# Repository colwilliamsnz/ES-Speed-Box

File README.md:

# ES-Speed-Box for controlling Pro-Ject Turntables with 16VAC Synchronous Motors.

## Status:

Prototype.

## Introduction:

A speed controller to suit Pro-Ject Turntables with 16VAC synchronous motors (Expression 3, etc). A clone of sorts of the off the shelf line of Pro-ject "SpeedBox" devices that allows for 33RPM and 45RPM speed selection electronically instead of changing the belt/pulley beneath the turntable platter.

Speed selection is controlled in software using a DDS (direct digital synthesis) IC to generate a sinusoidal waveform of the appropriate frequency (~50Hz for 33RPM, ~67 for 45RPM). An I2C header allows for an optional external OLED screen to display speed selection. An 18VDC output provides power to a Pro-Ject Phonobox. The device can be WiFi enabled to allow the speed to be controlled remotely using MQTT auto-discovery via HomeAssistant.

Power to the circuit is controlled via an SSR (solid state relay) and is intended to be connected to a 12V amplifier trigger output. Thus the device has no phantom power draw and only powers the turntable when the amplifier trigger output is on.

## Project Goals:

1. Powered on when the amplifier is on/phono aux input is on.
2. Provide power to both the turntable but also an Phono Box II pre-amp.
3. I2C interface to allow connection of an OLED screen to display speed and amp volume (amp volume via Yamaha API).
4. Low profile design to fit in a small rack mountable case.

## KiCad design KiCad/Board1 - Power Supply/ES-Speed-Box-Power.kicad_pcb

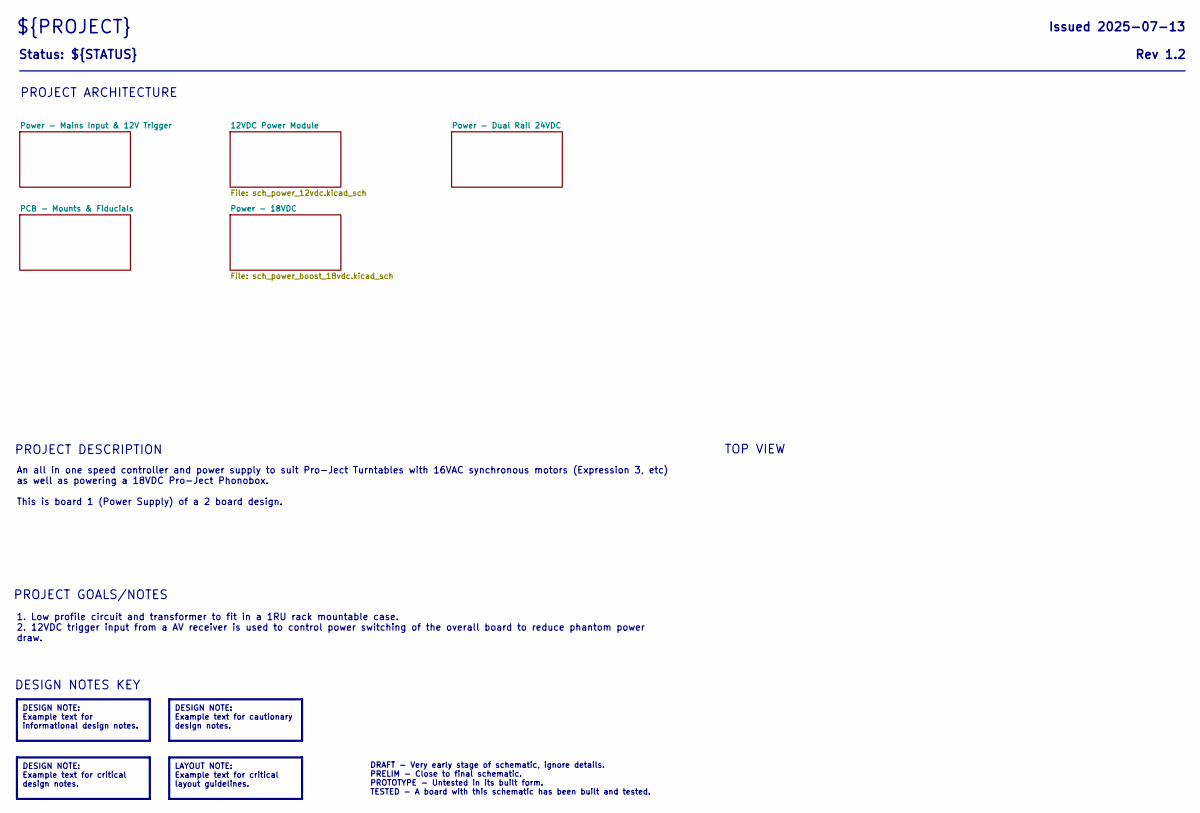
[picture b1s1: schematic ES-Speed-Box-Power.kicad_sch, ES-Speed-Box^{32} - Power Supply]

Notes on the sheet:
TOP VIEW
PROJECT DESCRIPTION
PROJECT GOALS/NOTES
PROJECT ARCHITECTURE
DESIGN NOTES KEY
${PROJECT}
Status: ${STATUS}
1. Low profile circuit and transformer to fit in a 1RU rack mountable case. 2. 12VDC trigger input from a AV receiver is used to control power switching of the overall board to reduce phantom power draw.
DESIGN NOTE: Example text for critical design notes.
DESIGN NOTE: Example text for cautionary design notes.
Issued ${ISSUE_DATE}
Rev ${REVISION}
LAYOUT NOTE: Example text for critical layout guidelines.
DRAFT - Very early stage of schematic, ignore details. PRELIM - Close to final schematic. PROTOTYPE - Untested in its built form. TESTED - A board with this schematic has been built and tested.
An all in one speed controller and power supply to suit Pro-Ject Turntables with 16VAC synchronous motors (Expression 3, etc) as well as powering a 18VDC Pro-Ject Phonobox. This is board 1 (Power Supply) of a 2 board design.
DESIGN NOTE: Example text for informational design notes.

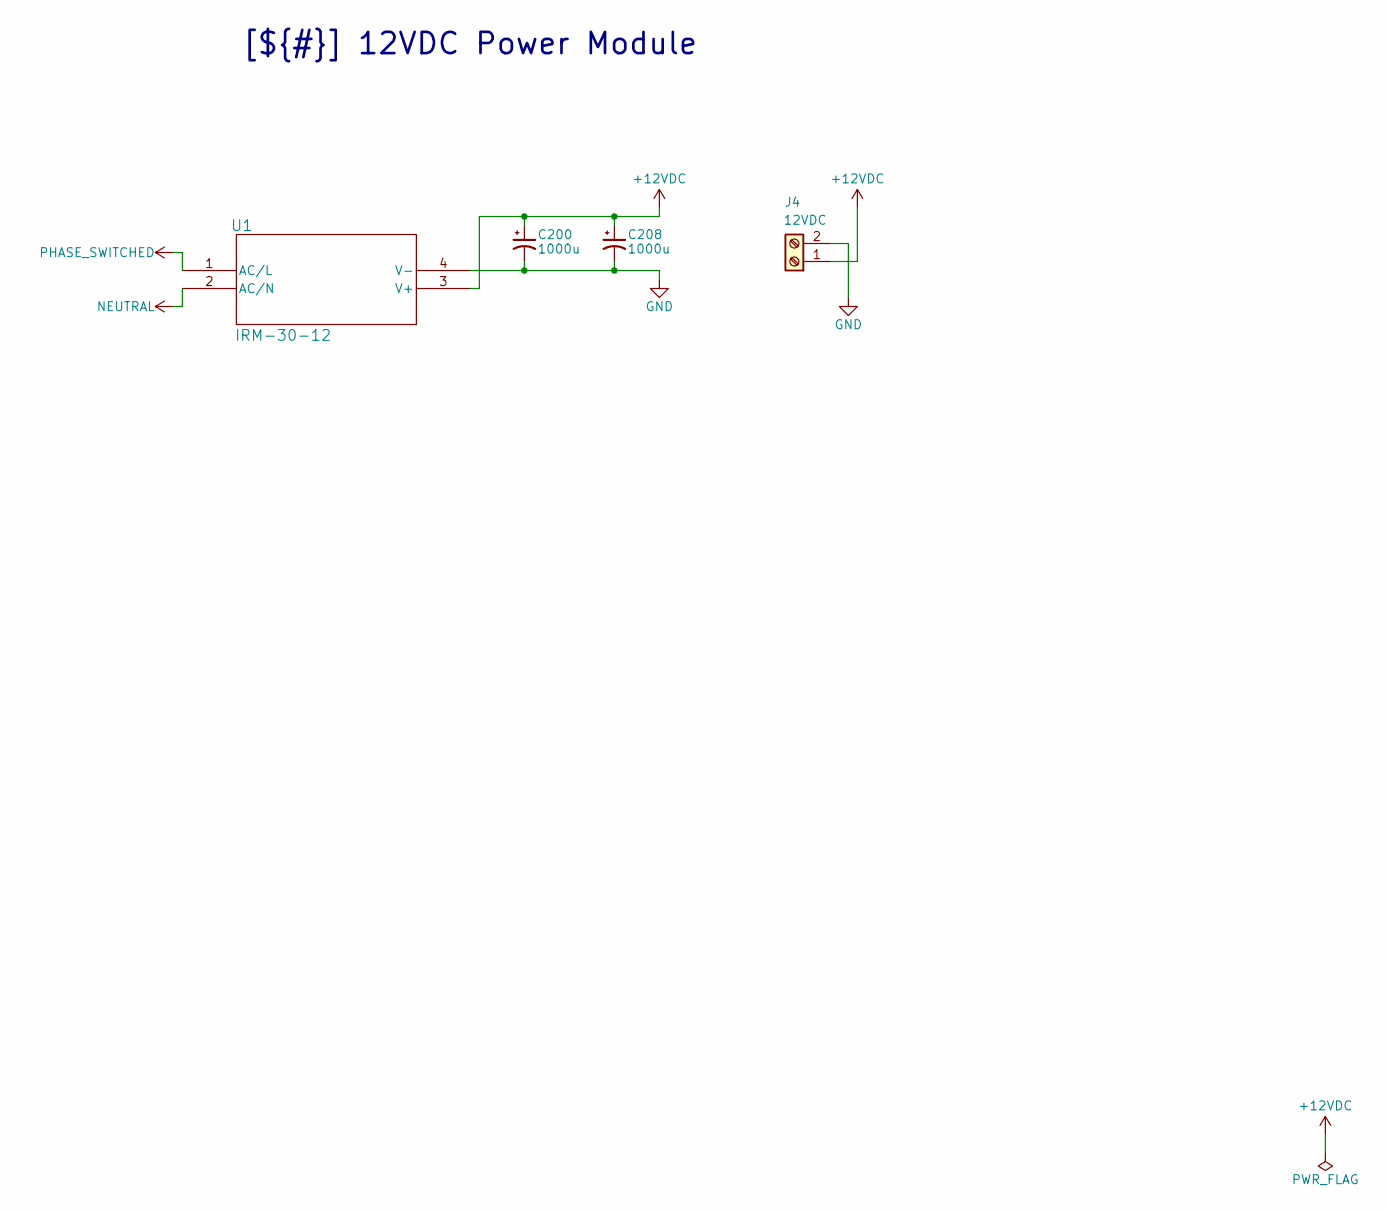
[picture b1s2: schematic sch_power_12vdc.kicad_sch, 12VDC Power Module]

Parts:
C200, C208: 1000u; CP_Radial_D13.0mm_P5.00mm
J4: 12VDC; TerminalBlock_1x02_P5.00mm
U1: IRM-30-12; Digikey_PN 1866-3043-ND

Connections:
+12VDC: C200.1, C208.1, J4.1, U1.3 (V+); also elsewhere on the board
GND: C200.2, C208.2, J4.2, U1.4 (V-); also elsewhere on the board
NEUTRAL: U1.2 (AC/N); also elsewhere on the board
PHASE_SWITCHED: U1.1 (AC/L); also elsewhere on the board

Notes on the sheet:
[${#}] ${TITLE}

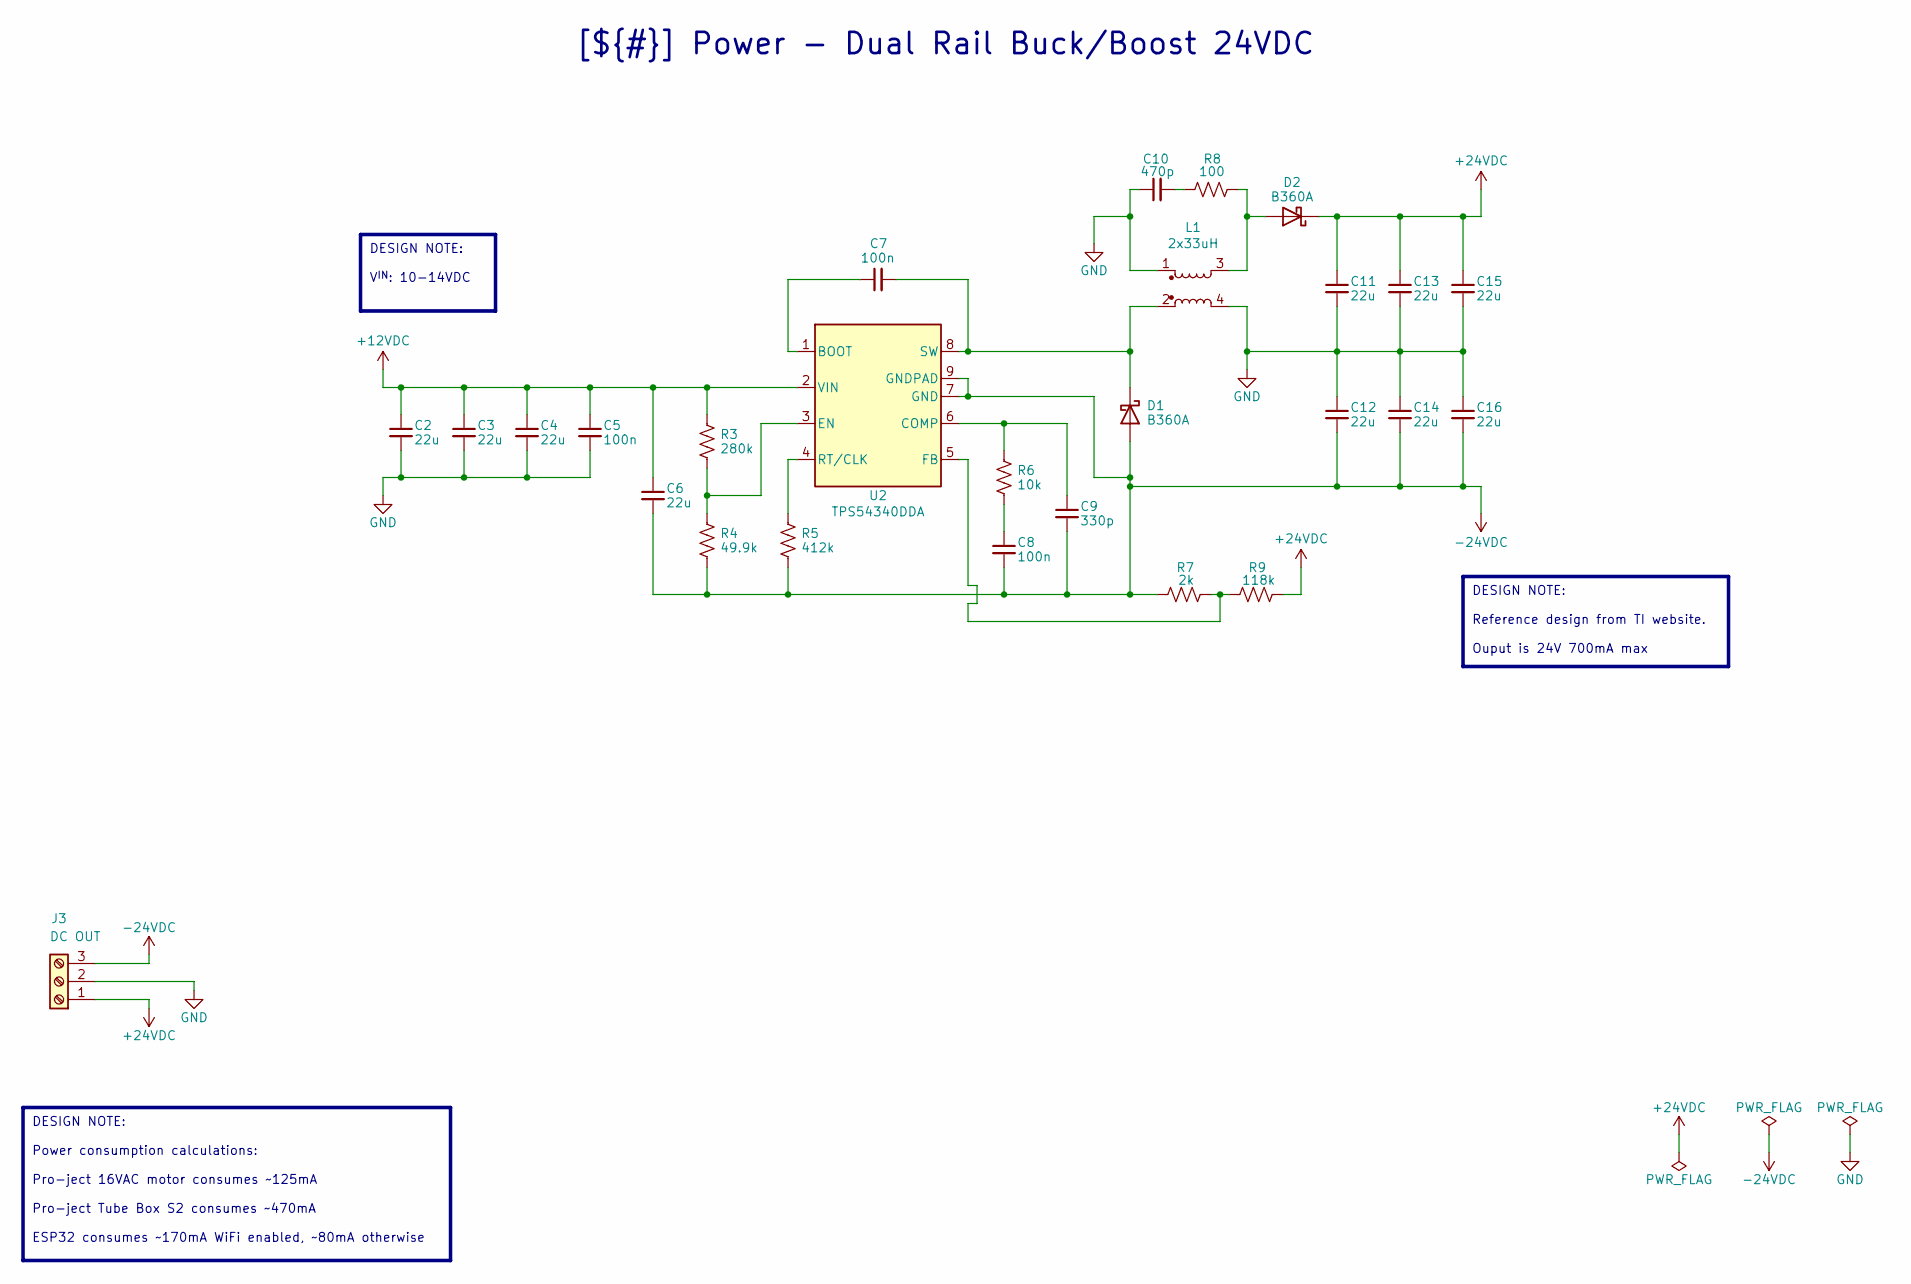
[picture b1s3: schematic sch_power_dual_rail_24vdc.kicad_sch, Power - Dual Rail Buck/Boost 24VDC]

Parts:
C2, C3, C4, C6, C11, C12, C13, C14, C15, C16: 22u; C_0805_2012Metric; Digikey_PN 445-14428-1-ND
C5, C7, C8: 100n; C_0603_1608Metric; Digikey_PN 587-3354-1-ND
C9: 330p; C_0603_1608Metric; Digikey_PN 399-C0603C331K5RACTUCT-ND
C10: 470p; C_0603_1608Metric; Digikey_PN 399-C0603C471F5GACTUCT-ND
D1, D2: B360A; D_SMA; Digikey_PN B360A-M3/61TGICT-ND
J3: DC OUT; TerminalBlock_1x03_P5.00mm
L1: 2x33uH; Bournes_SRF1260-330M; Digikey_PN SRF1260-330MCT-ND
R3: 280k; R_0603_1608Metric; Digikey_PN 311-280KHRCT-ND
R4: 49.9k; R_0603_1608Metric; Digikey_PN 541-3989-1-ND
R5: 412k; R_0603_1608Metric; Digikey_PN 311-412KHRCT-ND
R6: 10k; R_0603_1608Metric; Digikey_PN A121523CT-ND
R7: 2k; R_0603_1608Metric; Digikey_PN 541-3953-1-ND
R8: 100; R_0603_1608Metric; Digikey_PN 311-100HRCT-ND
R9: 118k; R_0603_1608Metric; Digikey_PN 541-118KHCT-ND
U2: TPS54340DDA; TI_SO-PowerPAD-8_ThermalVias; Digikey_PN 296-35495-5-ND

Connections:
+12VDC: C2.1, C3.1, C4.1, C5.1, C6.1, R3.1, U2.2 (VIN); also elsewhere on the board
+24VDC: C11.1, C13.1, C15.1, D2.1 (K), J3.1, R9.2
-24VDC: C6.2, C8.2, C9.2, C12.2, C14.2, C16.2, D1.2 (A), J3.3, R4.2, R5.2, R7.1, U2.7 (GND), U2.9 (GNDPAD)
GND: C2.2, C3.2, C4.2, C5.2, C10.1, C11.2, C12.1, C13.2, C14.1, C15.2, C16.1, J3.2, L1.1, L1.4; also elsewhere on the board
unnamed: C8.1, R6.2
unnamed: C10.2, R8.1
unnamed: C7.2, D1.1 (K), L1.2, U2.8 (SW)
unnamed: D2.2 (A), L1.3, R8.2
unnamed: C7.1, U2.1 (BOOT)
unnamed: C9.1, R6.1, U2.6 (COMP)
unnamed: R3.2, R4.1, U2.3 (EN)
unnamed: R7.2, R9.1, U2.5 (FB)
unnamed: R5.1, U2.4 (RT/CLK)

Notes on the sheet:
[${#}] ${TITLE}
DESIGN NOTE: Power consumption calculations: Pro-ject 16VAC motor consumes ~125mA Pro-ject Tube Box S2 consumes ~470mA ESP32 consumes ~170mA WiFi enabled, ~80mA otherwise
DESIGN NOTE: Reference design from TI website. Ouput is 24V 700mA max
DESIGN NOTE: V^{IN}: 10-14VDC

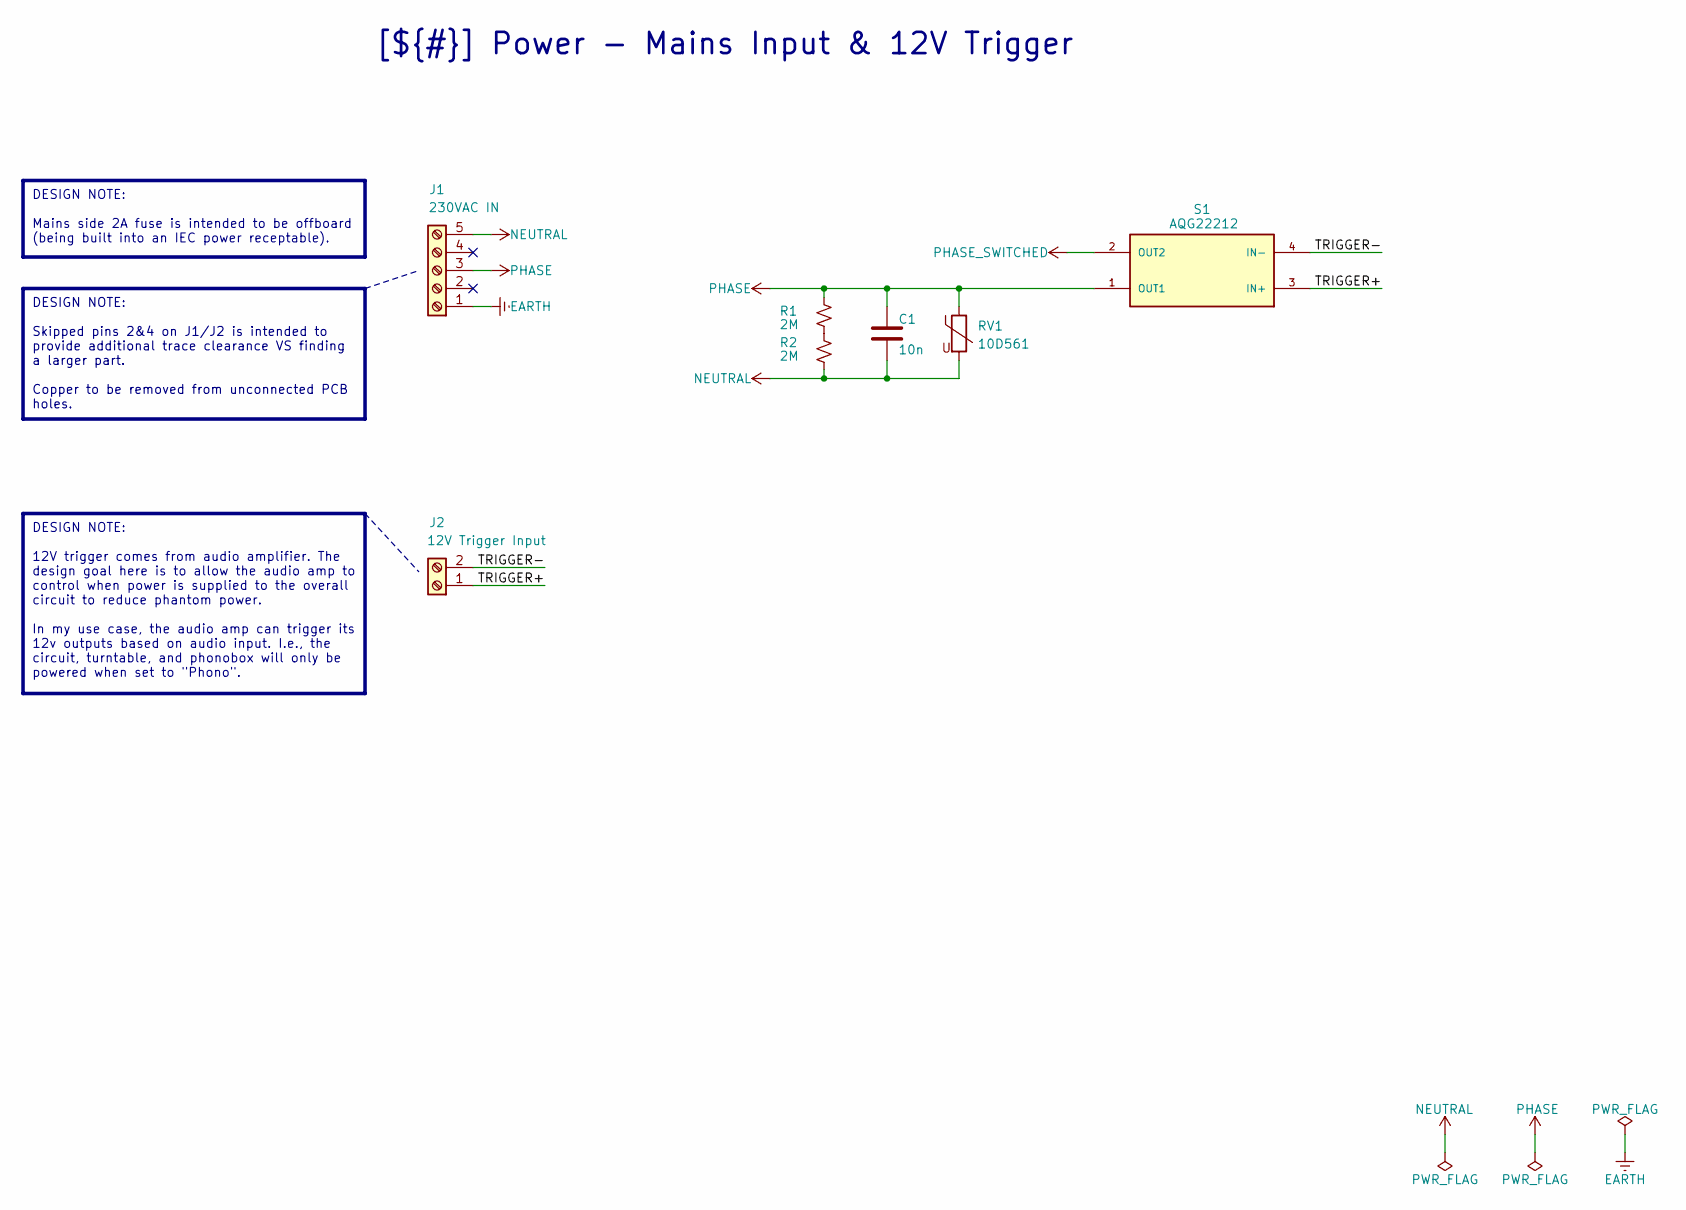
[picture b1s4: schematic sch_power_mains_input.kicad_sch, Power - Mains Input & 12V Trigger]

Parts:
C1: 10n; C_Rect_L18.0mm_W5.0mm_P15.00mm_FKS3_FKP3; Digikey_PN BFC233841103-ND
J1: 230VAC IN; TerminalBlock_1x05_P5.00mm
J2: 12V Trigger Input; TerminalBlock_1x02_P5.00mm
R1, R2: 2M; R_2010_5025Metric_Pad1.40x2.65mm_HandSolder; Digikey_PN 2019-HV732HTTE2004FCT-ND
RV1: 10D561; RV_Disc_D12mm_W6.1mm_P7.5mm; Digikey_PN 118-MOV-10D561K-ND
S1: AQG22212; Digikey_PN 255-3751-ND

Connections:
/Power - Mains Input & 12V Trigger/TRIGGER+: J2.1, S1.3 (IN+)
/Power - Mains Input & 12V Trigger/TRIGGER-: J2.2, S1.4 (IN-)
EARTH: J1.1
NEUTRAL: C1.2, J1.5, R2.2, RV1.2; also elsewhere on the board
unnamed: R1.2, R2.1
PHASE: C1.1, J1.3, R1.1, RV1.1, S1.1 (OUT1)
PHASE_SWITCHED: S1.2 (OUT2); also elsewhere on the board

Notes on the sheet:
DESIGN NOTE: Skipped pins 2&4 on J1/J2 is intended to provide additional trace clearance VS finding a larger part. Copper to be removed from unconnected PCB holes.
[${#}] ${TITLE}
DESIGN NOTE: 12V trigger comes from audio amplifier. The design goal here is to allow the audio amp to control when power is supplied to the overall circuit to reduce phantom power. In my use case, the audio amp can trigger its 12v outputs based on audio input. I.e., the circuit, turntable, and pho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
DESIGN NOTE: Mains side 2A fuse is intended to be offboard (being built into an IEC power receptable).

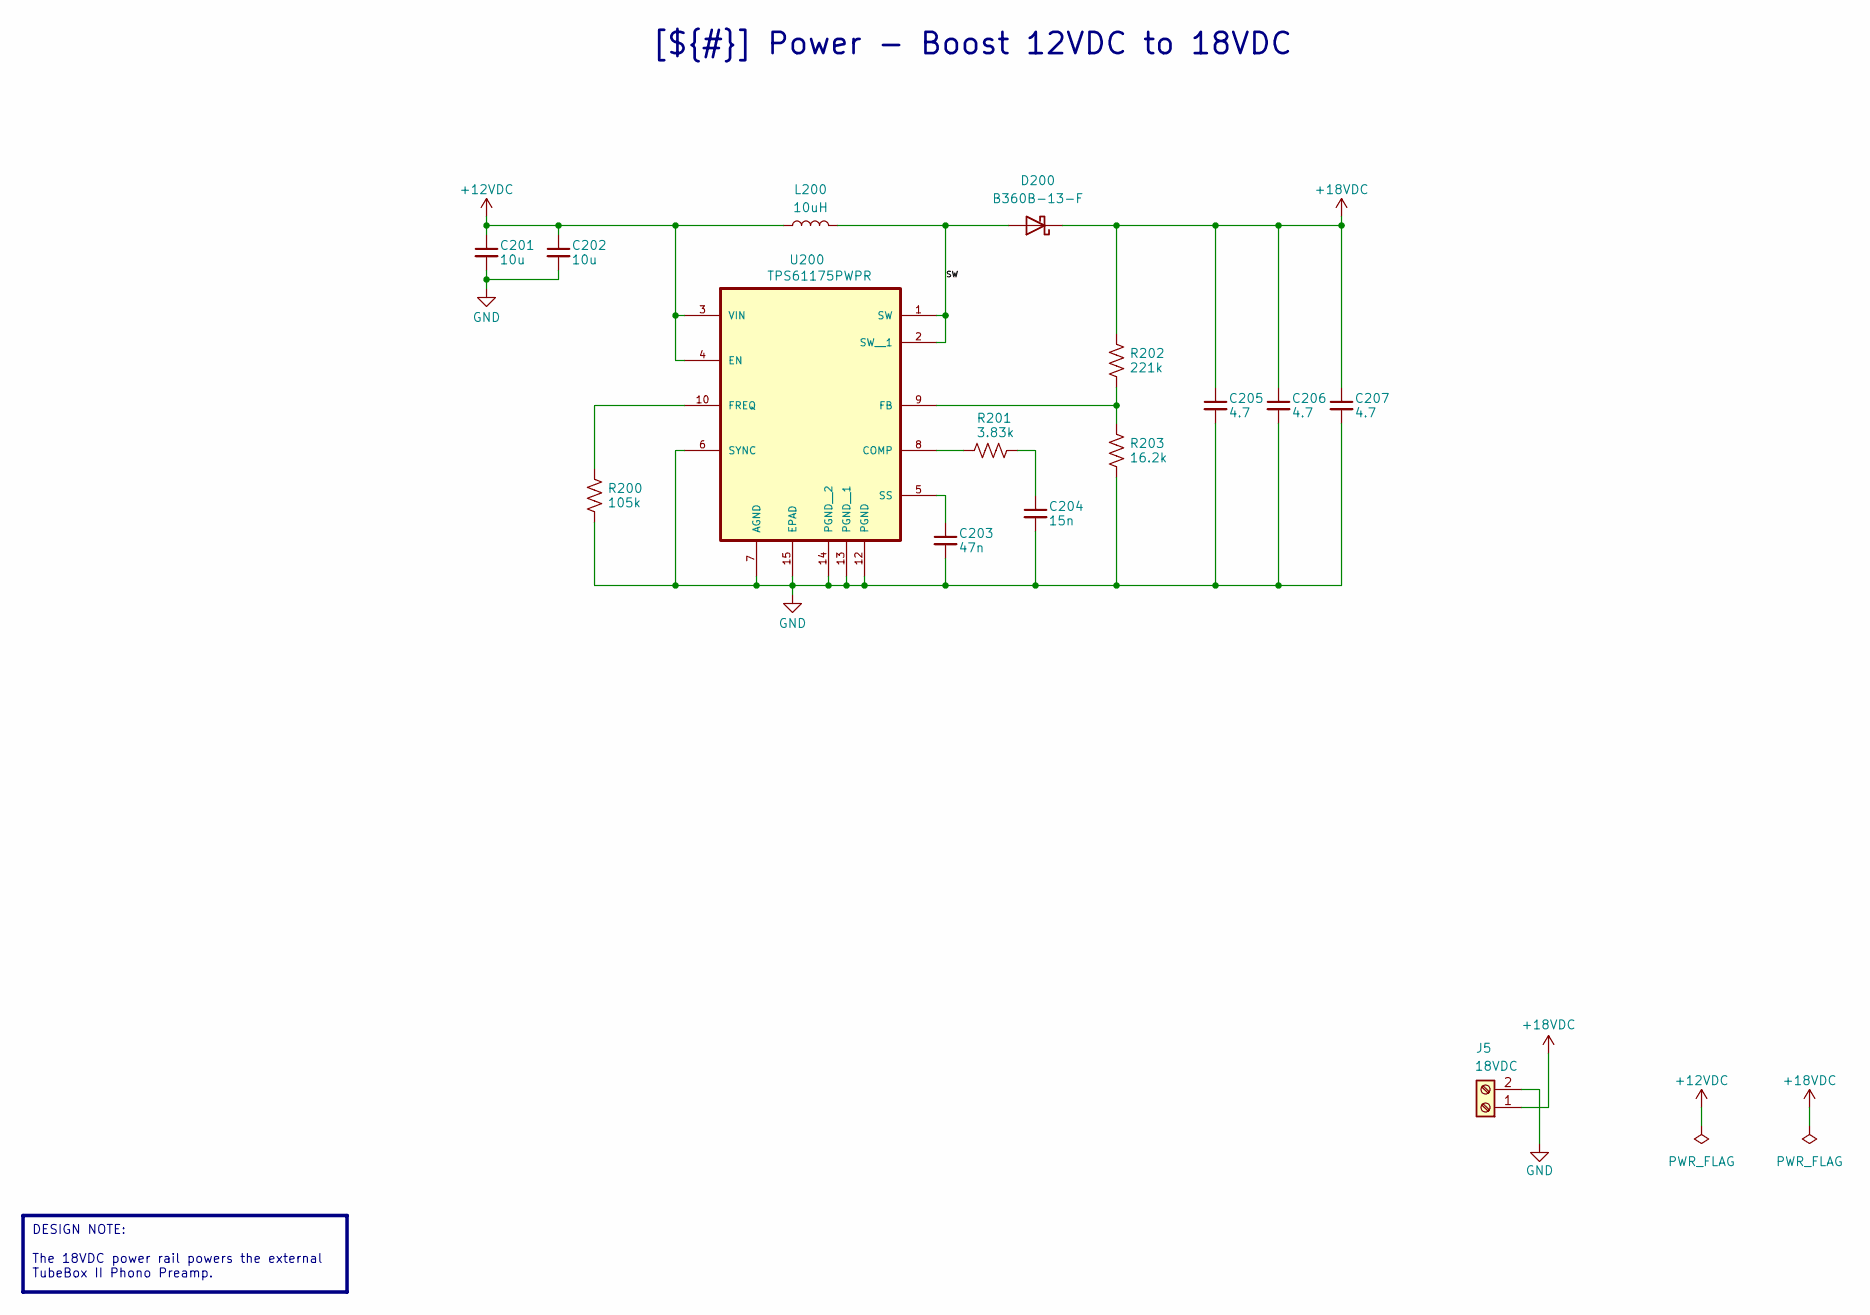
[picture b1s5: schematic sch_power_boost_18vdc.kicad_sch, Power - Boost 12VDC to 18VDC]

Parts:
C201, C202: 10u; C_0805_2012Metric; Digikey_PN 490-10515-1-ND
C203: 47n; C_0603_1608Metric; Digikey_PN 490-5854-1-ND
C204: 15n; C_0603_1608Metric; Digikey_PN 311-1430-1-ND
C205, C206, C207: 4.7; C_0805_2012Metric; Digikey_PN 490-10751-1-ND
D200: B360B-13-F; D_SMB; Digikey_PN B360B-FDICT-ND
J5: 18VDC; TerminalBlock_1x02_P5.00mm
L200: 10uH; Bournes_SRP5030T-100M; Digikey_PN SRP5030T-100MCT-ND
R200: 105k; R_0603_1608Metric; Digikey_PN 13-AC0603FR-07105KLCT-ND
R201: 3.83k; R_0603_1608Metric; Digikey_PN 311-3.83KHRCT-ND
R202: 221k; R_0603_1608Metric; Digikey_PN 311-221KHRCT-ND
R203: 16.2k; R_0603_1608Metric; Digikey_PN 311-16.2KHRCT-ND
U200: TPS61175PWPR; TPS61175; Digikey_PN 296-24013-1-ND

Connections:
+12VDC: C201.1, C202.1, L200.1, U200.3 (VIN), U200.4 (EN); also elsewhere on the board
+18VDC: C205.1, C206.1, C207.1, D200.1 (K), J5.1, R202.1
/Power - 18VDC/SW: D200.2 (A), L200.2, U200.1 (SW), U200.2 (SW__1)
GND: C201.2, C202.2, C203.2, C204.2, C205.2, C206.2, C207.2, J5.2, R200.2, R203.2, U200.6 (SYNC), U200.7 (AGND), U200.12 (PGND), U200.13 (PGND__1), U200.14 (PGND__2), U200.15 (EPAD); also elsewhere on the board
unnamed: C204.1, R201.2
unnamed: R201.1, U200.8 (COMP)
unnamed: R202.2, R203.1, U200.9 (FB)
unnamed: R200.1, U200.10 (FREQ)
unnamed: C203.1, U200.5 (SS)

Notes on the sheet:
DESIGN NOTE: The 18VDC power rail powers the external TubeBox II Phono Preamp.
[${#}] ${TITLE}

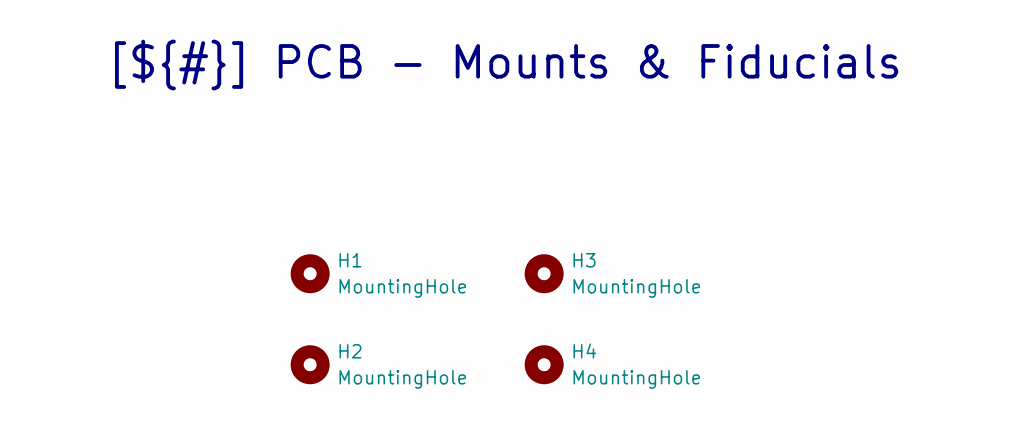
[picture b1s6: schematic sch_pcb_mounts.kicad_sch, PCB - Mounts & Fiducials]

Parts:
H1, H2, H3, H4: MountingHole; MountingHole_2.2mm_M2

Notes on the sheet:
[${#}] ${TITLE}

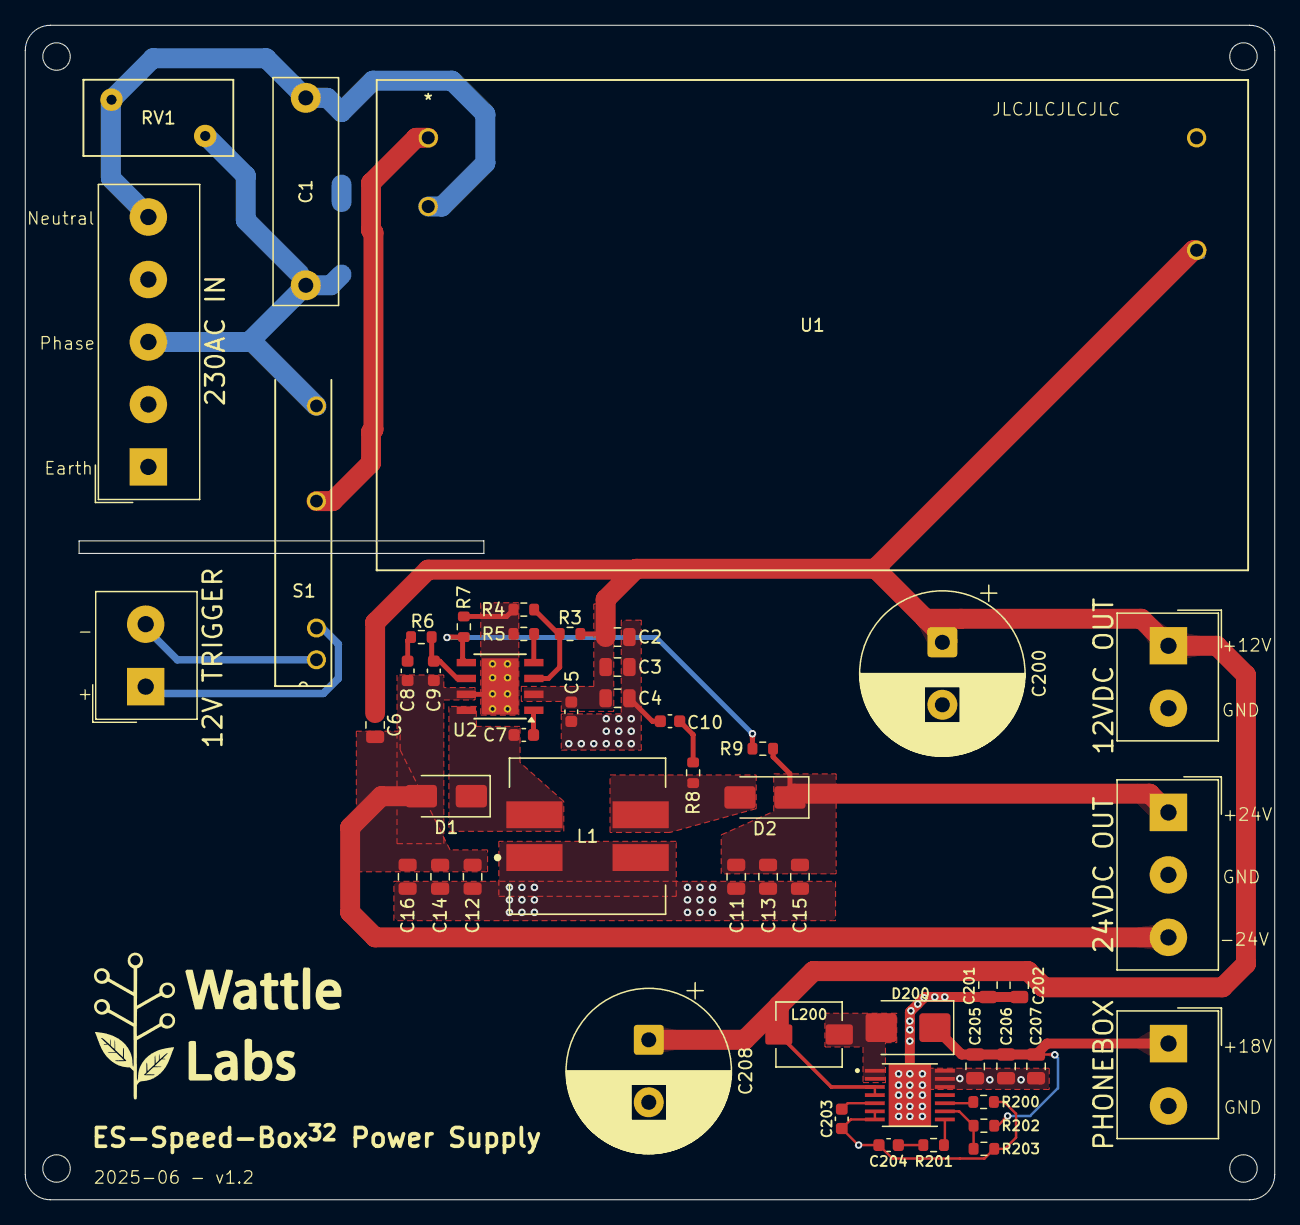
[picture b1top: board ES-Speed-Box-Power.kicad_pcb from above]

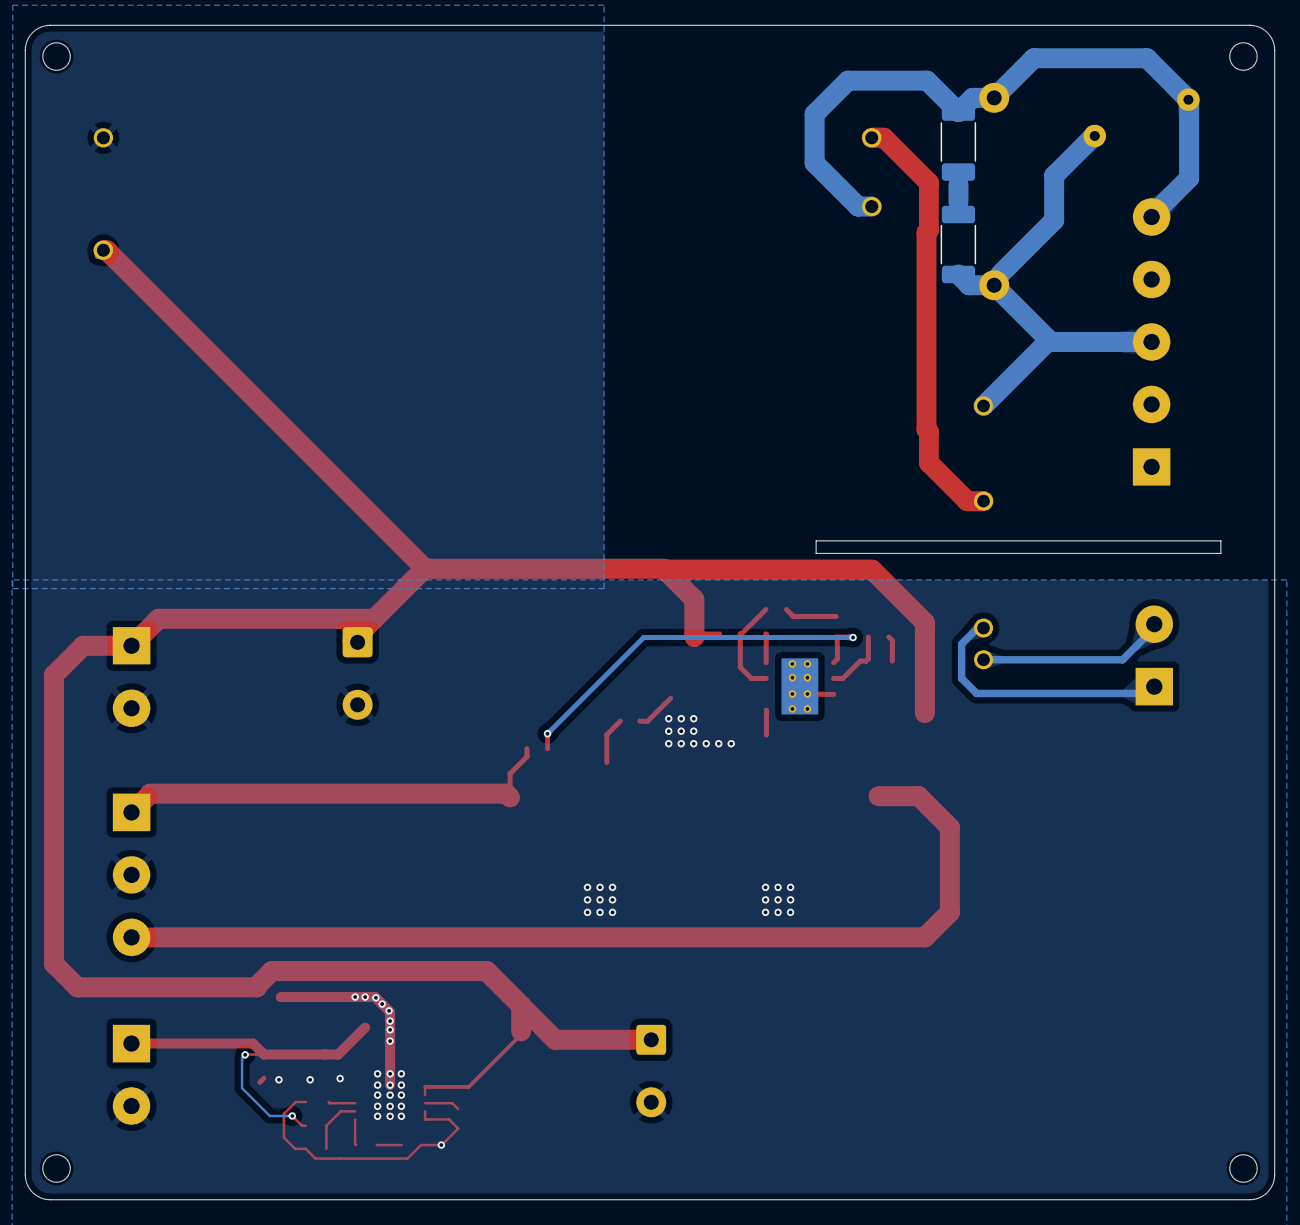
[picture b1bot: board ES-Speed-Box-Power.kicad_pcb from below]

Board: 2 copper layers, 100.0 x 94.0 mm, 57 parts (2 on the bottom side), 26 nets.

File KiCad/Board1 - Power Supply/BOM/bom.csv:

"Reference","Value","Footprint","Qty","Digikey_PN"
"C1","10n","Capacitor_THT:C_Rect_L18.0mm_W5.0mm_P15.00mm_FKS3_FKP3","1","BFC233841103-ND"
"C2,C3,C4,C6,C11,C12,C13,C14,C15,C16","22u","Capacitor_SMD:C_0805_2012Metric","10","445-14428-1-ND"
"C5,C7,C8","100n","Capacitor_SMD:C_0603_1608Metric","3","587-3354-1-ND"
"C9","330p","Capacitor_SMD:C_0603_1608Metric","1","399-C0603C331K5RACTUCT-ND"
"C10","470p","Capacitor_SMD:C_0603_1608Metric","1","399-C0603C471F5GACTUCT-ND"
"C200,C208","1000u","Capacitor_THT:CP_Radial_D13.0mm_P5.00mm","2",""
"C201,C202","10u","Capacitor_SMD:C_0805_2012Metric","2","490-10515-1-ND"
"C203","47n","Capacitor_SMD:C_0603_1608Metric","1","490-5854-1-ND"
"C204","15n","Capacitor_SMD:C_0603_1608Metric","1","311-1430-1-ND"
"C205,C206,C207","4.7","Capacitor_SMD:C_0805_2012Metric","3","490-10751-1-ND"
"D1,D2","B360A","Diode_SMD:D_SMA","2","B360A-M3/61TGICT-ND"
"D200","B360B-13-F","Diode_SMD:D_SMB","1","B360B-FDICT-ND"
"L1","2x33uH","Wattle_Inductors:Bournes_SRF1260-330M","1","SRF1260-330MCT-ND"
"L200","10uH","Wattle_Inductors:Bournes_SRP5030T-100M","1","SRP5030T-100MCT-ND"
"R1,R2","2M","Resistor_SMD:R_2010_5025Metric_Pad1.40x2.65mm_HandSolder","2","2019-HV732HTTE2004FCT-ND"
"R3","280k","Resistor_SMD:R_0603_1608Metric","1","311-280KHRCT-ND"
"R4","49.9k","Resistor_SMD:R_0603_1608Metric","1","541-3989-1-ND"
"R5","412k","Resistor_SMD:R_0603_1608Metric","1","311-412KHRCT-ND"
"R6","10k","Resistor_SMD:R_0603_1608Metric","1","A121523CT-ND"
"R7","2k","Resistor_SMD:R_0603_1608Metric","1","541-3953-1-ND"
"R8","100","Resistor_SMD:R_0603_1608Metric","1","311-100HRCT-ND"
"R9","118k","Resistor_SMD:R_0603_1608Metric","1","541-118KHCT-ND"
"R200","105k","Resistor_SMD:R_0603_1608Metric","1","13-AC0603FR-07105KLCT-ND"
"R201","3.83k","Resistor_SMD:R_0603_1608Metric","1","311-3.83KHRCT-ND"
"R202","221k","Resistor_SMD:R_0603_1608Metric","1","311-221KHRCT-ND"
"R203","16.2k","Resistor_SMD:R_0603_1608Metric","1","311-16.2KHRCT-ND"
"RV1","10D561","Varistor:RV_Disc_D12mm_W6.1mm_P7.5mm","1","118-MOV-10D561K-ND"
"S1","AQG22212","Wattle_Relays:AQG22212","1","255-3751-ND"
"U1","IRM-30-12","Wattle_Power:IRM-30-12","1","1866-3043-ND"
"U2","TPS54340DDA","Package_SO:TI_SO-PowerPAD-8_ThermalVias","1","296-35495-5-ND"
"U200","TPS61175PWPR","Wattle_Regulators:TPS61175","1","296-24013-1-ND"

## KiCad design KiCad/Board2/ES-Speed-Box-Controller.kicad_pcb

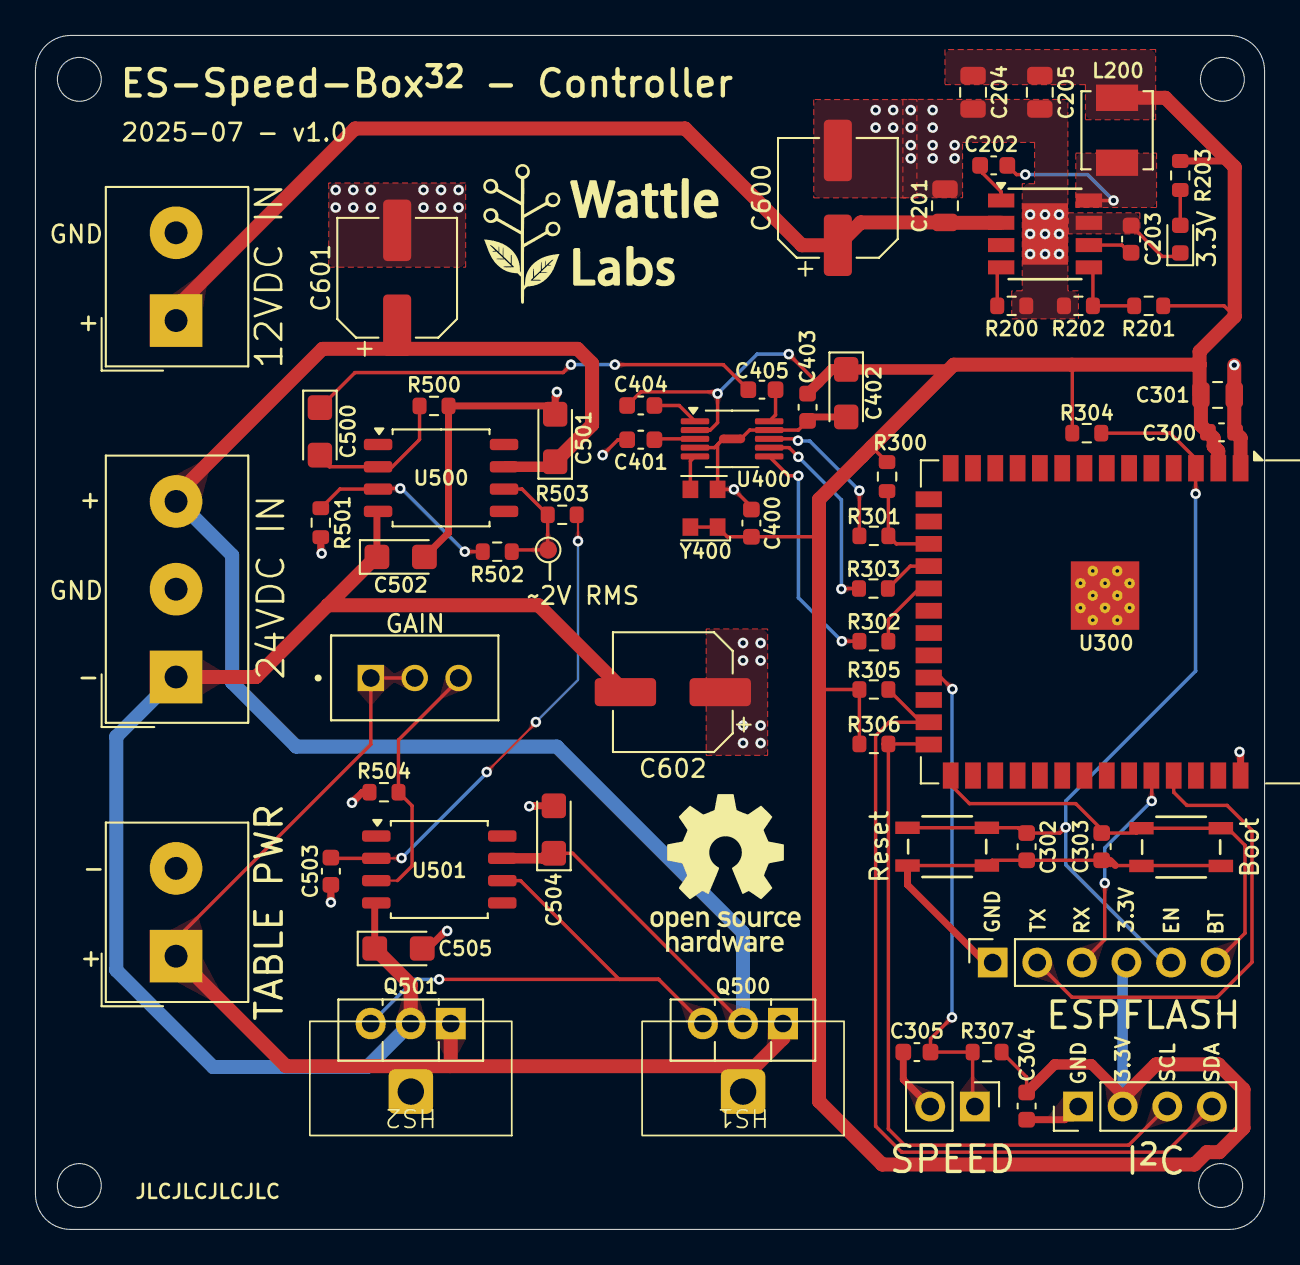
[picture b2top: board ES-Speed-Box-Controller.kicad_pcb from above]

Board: 2 copper layers, 70.0 x 68.0 mm, 70 parts (0 on the bottom side), 37 nets.

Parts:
C201, C204, C205, C301: 22u; C_0805_2012Metric
C202, C300, C302, C303, C304, C305, C400, C401, C403: 100n; C_0603_1608Metric
C203, C404: 10n; C_0603_1608Metric
C402, C500: 10u; CP_EIA-3216-18_Kemet-A
C405: 10p; C_0603_1608Metric
C501, C502, C504, C505: 1u; CP_EIA-3216-18_Kemet-A
C503: 470n; C_0603_1608Metric
C600, C601, C602: 47u; CP_Elec_6.3x7.7
D200: 3.3V; LED_0603_1608Metric
H1, H2, H3, H4: MountingHole; MountingHole_2.5mm
HS1, HS2: Heatsink; V5629
J300: ESPFlash; PinSocket_1x06_P2.54mm_Vertical
J301: I2C; PinHeader_1x04_P2.54mm_Vertical
J302: Speed; PinHeader_1x02_P2.54mm_Vertical
J600: 12VDC; TerminalBlock_1x02_P5.00mm
J601: 24VDC; TerminalBlock_1x03_P5.00mm
J602: Turntable Power; TerminalBlock_1x02_P5.00mm
L200: 4.7uH; Bournes_SRP4020TA-4R7M
NT400: NetTie_2; NetTie-2_SMD_Pad0.5mm
Q500: BD139; TO-126-3_Vertical
Q501: BD140; TO-126-3_Vertical
R200: 200k; R_0603_1608Metric
R201: 69.8k; R_0603_1608Metric
R202: 22.1k; R_0603_1608Metric
R203: 1k5; R_0603_1608Metric
R300, R304, R307: 10k; R_0603_1608Metric
R301, R302, R303: 100; R_0603_1608Metric
R305, R306: 4k7; R_0603_1608Metric
R500, R501, R502, R504: 1k; R_0603_1608Metric
R503: 0R; R_0603_1608Metric
RV500: 10k; PV36W103C01B00
SW300: Reset; PTS810
SW301: Boot; PTS810
TP500: ~2V RMS; TestPoint_Pad_D1.0mm
U200: AP64352Q; AP64352QSP-13
U300: ESP32-S3-WROOM-1
U400: AD9833BRMZ; MSOP-10_3x3mm_P0.5mm
U500, U501: OPA604AU/2K5; SOIC-8_5.3x5.3mm_P1.27mm
Y400: 24Mhz; Oscillator_SMD_EuroQuartz_XO32-4Pin_3.2x2.5mm

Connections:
+3.3VDC: C204.1, C205.1, C300.1, C301.1, C304.1, C400.1, C402.1, C403.2, C404.1, J300.4, J301.2, L200.2, R201.1, R203.1, R300.2, R304.2, R305.1, R306.1, R307.2, U300.2 (3V3), U400.2 (VDD), Y400.1 (EN), Y400.4 (V+)
+12VDC: C201.1, C600.1, J600.1, U200.2 (VIN)
+24VDC: C501.1, C504.1, C601.1, J601.3, Q500.2 (C), U500.7 (VS+), U501.7 (VS+)
-24VDC: C502.1, C505.1, C602.2, J601.1, Q501.2 (C), U500.4 (VS-), U501.4 (VS-)
/IO - AD9833 DDS/DDS_OUT: C405.1, C500.1
/IO - AD9833 DDS/SPI_CLK: R303.2, U400.7 (SCLK)
/IO - AD9833 DDS/SPI_CS: R301.2, U400.8 (~FSYNC)
/IO - AD9833 DDS/SPI_MOSI: R302.2, U400.6 (SDATA)
/IO - Power Connectors/POWER_AMP_OUT: J602.1, Q500.1 (E), Q501.1 (E), RV500.1, RV500.2
/MCU - ESP32S3/BOOT: C303.1, J300.6, SW301.3 (K), SW301.4 (A), U300.27 (IO0)
/MCU - ESP32S3/CLK: R303.1, U300.18 (IO10)
/MCU - ESP32S3/CS: R300.1, R301.1, U300.17 (IO9)
/MCU - ESP32S3/ENABLE: C302.1, J300.5, R304.1, SW300.3 (K), SW300.4 (A), U300.3 (EN)
/MCU - ESP32S3/ESP_RXD: J300.3, U300.36 (RXD0)
/MCU - ESP32S3/ESP_TXD: J300.2, U300.37 (TXD0)
/MCU - ESP32S3/I2C_SCL: J301.3, R306.2, U300.26 (IO45)
/MCU - ESP32S3/I2C_SDA: J301.4, R305.2, U300.25 (IO48)
/MCU - ESP32S3/MOSI: R302.1, U300.19 (IO11)
/MCU - ESP32S3/SPEED: C305.1, J302.1, R307.1, U300.23 (IO21)
AGND: C402.2, C403.1, NT400.2, U400.9 (AGND)
GND: C201.2, C203.2, C204.2, C205.2, C300.2, C301.2, C302.2, C303.2, C304.2, C305.2, C400.2, C401.2, C501.2, C502.2, C503.2, C504.2, C505.2, C600.2, C601.2, C602.1, D200.1 (K), J300.1, J301.1, J302.2, J600.2, J601.2, J602.2, NT400.1, R200.2, R202.2, R500.2, R501.2, R504.2, SW300.1, SW300.2, SW301.1, SW301.2, U200.7 (GND), U200.9 (GND), U300.1 (GND), U300.40 (GND), U300.41 (GND), U400.4 (DGND), Y400.2 (GND)
unnamed: D200.2 (A), R203.2
unnamed: Q500.3 (B), Q501.3 (B), U501.6 (OUT)
unnamed: C202.2, U200.1 (BST)
unnamed: R201.2, R202.1, U200.5 (FB)
unnamed: R200.1, U200.4 (RT/CLK)
unnamed: C203.1, U200.6 (SS)
unnamed: C202.1, L200.1, U200.8 (SW)
unnamed: C401.1, U400.3 (CAP/2.5V)
unnamed: C404.2, U400.1 (COMP)
unnamed: U400.5 (MCLK), Y400.3 (OUT)
unnamed: C405.2, U400.10 (VOUT)
unnamed: R501.1, R502.2, U500.3 (IN+)
unnamed: C500.2, R500.1, U500.2 (IN-)
unnamed: R502.1, R503.2, TP500.1, U500.6 (OUT)
unnamed: R504.1, RV500.3, U501.3 (IN+)
unnamed: C503.1, R503.1, U501.2 (IN-)

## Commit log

2025-07-15 Update gitignore
2025-07-27 Tweaks to PCB
    DRC check exceptions. Produced gerbers for JLCPCB.
